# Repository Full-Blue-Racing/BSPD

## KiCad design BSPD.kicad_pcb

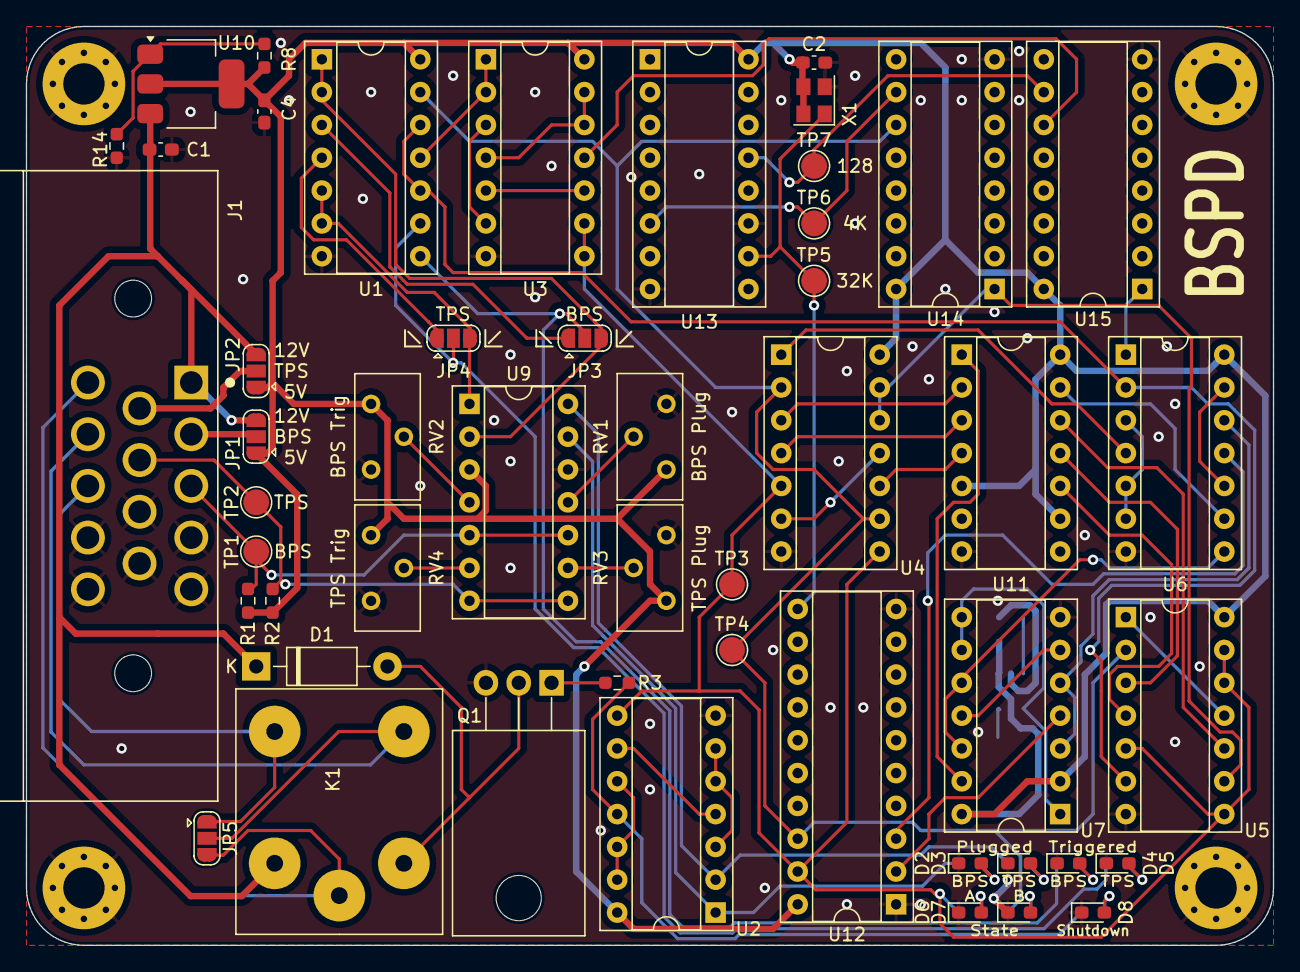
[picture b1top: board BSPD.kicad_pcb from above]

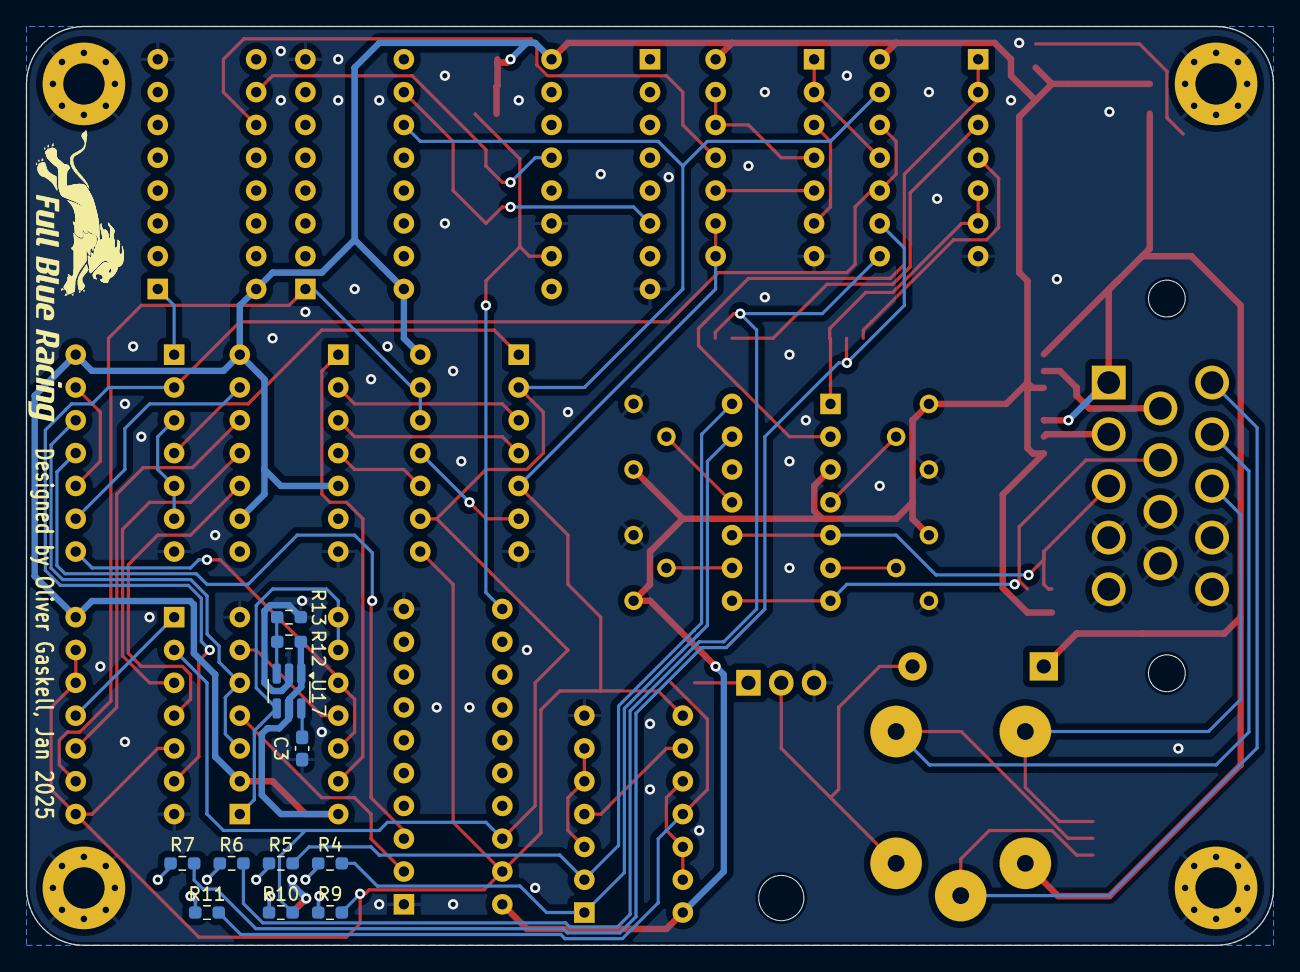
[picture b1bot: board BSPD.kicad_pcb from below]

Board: 2 copper layers, 96.5 x 71.1 mm, 65 parts (11 on the bottom side), 70 nets.

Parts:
C1: 0.1u; C_0603_1608Metric_Pad1.08x0.95mm_HandSolder
C2: 10u; C_0603_1608Metric_Pad1.08x0.95mm_HandSolder
C3: 200n; C_0603_1608Metric_Pad1.08x0.95mm_HandSolder
C4: 1u; C_0603_1608Metric_Pad1.08x0.95mm_HandSolder
D1: 1N5817; D_DO-41_SOD81_P10.16mm_Horizontal
D2, D3, D4, D5, D6, D7, D8: LED; LED_0603_1608Metric_Pad1.05x0.95mm_HandSolder
H1, H2, H3, H4: MountingHole_Pad; MountingHole_3.2mm_M3_Pad_Via
J1: Conn_01x14; TE_776267-1
JP1, JP2, JP3, JP4, JP5: SolderJumper_3_Open; SolderJumper-3_P1.3mm_Open_RoundedPad1.0x1.5mm
K1: MCCMA51-S-DC12V-C
Q1: IRLZ44Z; TO-220-3_Horizontal_TabDown
R1, R2: 100K; R_0603_1608Metric_Pad0.98x0.95mm_HandSolder
R3: 4.7k; R_0603_1608Metric_Pad0.98x0.95mm_HandSolder
R4, R5, R6, R7, R9, R10, R11: 180; R_0603_1608Metric_Pad0.98x0.95mm_HandSolder
R8: 240; R_0603_1608Metric_Pad0.98x0.95mm_HandSolder
R12: 750k; R_0603_1608Metric_Pad0.98x0.95mm_HandSolder
R13: 100k; R_0603_1608Metric_Pad0.98x0.95mm_HandSolder
R14: 715; R_0603_1608Metric_Pad0.98x0.95mm_HandSolder
RV1, RV2, RV3, RV4: 10k; Potentiometer_Bourns_3296Y_Vertical
TP1, TP2, TP3, TP4, TP5, TP6, TP7: TestPoint; TestPoint_Pad_D2.0mm
U1, U2, U3, U4, U5, U6, U7: 4011; DIP-14_W7.62mm_Socket
U9: TLC3704; DIP-14_W7.62mm_Socket
U10: LM317_SOT-223; SOT-223-3_TabPin2
U11: 4012; DIP-14_W7.62mm_Socket
U12: 74LS573; DIP-20_W7.62mm_Socket
U13, U14, U15: 4040; DIP-16_W7.62mm_Socket
U17: MAX6895; SOT-23-6_Handsoldering
X1: ASZKDV-32.768KHz; Oscillator_SMD_Abracon_ASE-4Pin_3.2x2.5mm

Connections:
+5V: C2.1, C4.1, JP1.1 (A), JP2.1 (A), R1.2, R2.2, R8.1, R12.1, RV1.1, RV2.1, RV3.1, RV4.1, U1.14 (VDD), U2.14 (VDD), U3.14 (VDD), U4.14 (VDD), U5.14 (VDD), U6.14 (VDD), U7.2, U7.14 (VDD), U9.3 (V+), U10.2 (VO), U11.5, U11.9, U11.14 (VDD), U12.20 (VCC), U13.16 (VDD), U14.16 (VDD), U15.16 (VDD), U17.1 (EN), U17.5 (VCC), X1.3 (OE), X1.4 (Vdd)
+12V: C1.1, D1.1 (K), J1.1, JP1.3 (B), JP2.3 (B), K1.A1, U10.3 (VI)
/BPS_Plugged: R4.2, U2.1, U9.13
/BPS_Power: J1.2, JP1.2 (C)
/BPS_Sig: J1.3, R1.1, TP1.1, U9.5 (+), U9.10 (-)
/BPS_Trig: JP3.2 (C), R6.2, U1.8
/CLK: TP5.1, U12.11 (Load), U13.10 (CLK), X1.1 (Out)
/RST: U7.1, U7.8, U7.9, U17.4 (OUT)
/SD_Sig: R3.1, R11.2, U2.11
/SM_Ok: R9.2, TP3.1, U2.8, U3.8, U3.9, U4.5, U4.8, U5.5, U5.8, U5.12, U5.13, U12.19 (Q0)
/ShutdownC: J1.10, JP5.3 (B), K1.11
/ShutdownNC: J1.11, JP5.2 (C), K1.12
/ShutdownNO: J1.12, JP5.1 (A), K1.14
/State Machine/5T: U4.12, U4.13, U5.9, U14.1 (Q11)
/State Machine/10T: U6.1, U15.1 (Q11)
/State Machine/State_B: R10.2, TP4.1, U1.13, U4.2, U4.9, U5.2, U12.18 (Q1), U14.11 (Reset)
/State Machine/Timers/128CLK: TP7.1, U13.13 (Q7), U15.10 (CLK)
/State Machine/Timers/4096CLK: TP6.1, U13.6 (Q2), U14.10 (CLK)
/State Machine/Timers/Reset_Counting: U3.11, U15.11 (Reset)
/System_OK: U1.10, U1.12, U5.6, U6.2
/TPS_Plugged: R5.2, U2.2, U9.14
/TPS_Power: J1.6, JP2.2 (C)
/TPS_Sig: J1.7, R2.1, TP2.1, U9.7 (+), U9.8 (-)
/TPS_Trig: JP4.2 (C), R7.2, U1.9
GND: C1.2, C2.2, C3.2, C4.2, D2.1 (K), D3.1 (K), D4.1 (K), D5.1 (K), D6.1 (K), D7.1 (K), D8.1 (K), H1.1, H2.1, H3.1, H4.1, J1.4, J1.5, J1.8, J1.9, J1.13, J1.14, Q1.3 (S), R13.2, R14.2, RV1.3, RV2.3, RV3.3, RV4.3, U1.7 (VSS), U2.7 (VSS), U3.7 (VSS), U4.7 (VSS), U5.7 (VSS), U6.7 (VSS), U7.7 (VSS), U9.12 (V-), U11.7 (VSS), U12.1 (OE), U12.10 (GND), U13.8 (VSS), U13.11 (Reset), U14.8 (VSS), U15.8 (VSS), U17.2 (GND), X1.2 (GND)
unnamed: D1.2 (A), K1.A2, Q1.2 (D)
unnamed: D2.2 (A), R4.1
unnamed: D3.2 (A), R5.1
unnamed: D4.2 (A), R6.1
unnamed: D5.2 (A), R7.1
unnamed: D6.2 (A), R9.1
unnamed: D7.2 (A), R10.1
unnamed: D8.2 (A), R11.1
unnamed: JP3.1 (A), U1.3
unnamed: JP3.3 (B), U1.1, U1.2, U9.2
unnamed: JP4.1 (A), U1.4
unnamed: JP4.3 (B), U1.5, U1.6, U9.1
unnamed: Q1.1 (G), R3.2
unnamed: U1.11, U3.1, U3.2
unnamed: U2.3, U2.5, U2.6
unnamed: U2.4, U2.9
unnamed: U2.10, U2.12, U2.13
unnamed: U3.3, U3.6
unnamed: U3.5, U3.10
unnamed: U3.4, U3.12, U3.13
unnamed: U4.1, U6.4
unnamed: U4.6, U4.11
unnamed: U5.1, U5.11
unnamed: U6.3, U6.5, U6.6
unnamed: U6.8, U7.10, U7.12
unnamed: U6.10, U6.13
unnamed: U6.12, U7.3, U7.5
unnamed: U7.6, U7.11
unnamed: RV2.2, U9.4 (-)
unnamed: RV4.2, U9.6 (-)
unnamed: RV1.2, U9.11 (+)
unnamed: RV3.2, U9.9 (+)
unnamed: R8.2, R14.1, U10.1 (ADJ)
unnamed: U7.13, U11.1
unnamed: U4.3, U11.2
unnamed: U4.4, U11.3
unnamed: U4.10, U11.4
unnamed: U5.4, U11.10
unnamed: U5.3, U11.11
unnamed: U5.10, U11.12
unnamed: U6.9, U11.13
unnamed: U7.4, U12.2 (D0)
unnamed: U6.11, U12.3 (D1)
unnamed: C3.1, U17.6 (CDELAY)
unnamed: R12.2, R13.1, U17.3 (IN)

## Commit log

2024-10-12 Initial Version.
    Same design as the FBR24, simply updated to use the correct symbol
    and footprint libraries.
2024-10-12 Add generated/ to gitignore.
2024-11-01 Switch reset driver to MAX6895
2024-11-01 Ignore ~*.lck (KiCad lock files)
2024-11-01 Update Relay symbol
2024-12-16 Complete new version
2024-12-16 Generate Gerbers
2025-01-10 Misc improvements and changes.
    - Updated some silkscreen
    - Added 2 more mounting holes, changed them to pads
    - Updated FBR Logo
2025-01-18 Small changes, post design review
    - Moving tracks away from PCB edge
    - Added jumper, can be used to short shutdown
